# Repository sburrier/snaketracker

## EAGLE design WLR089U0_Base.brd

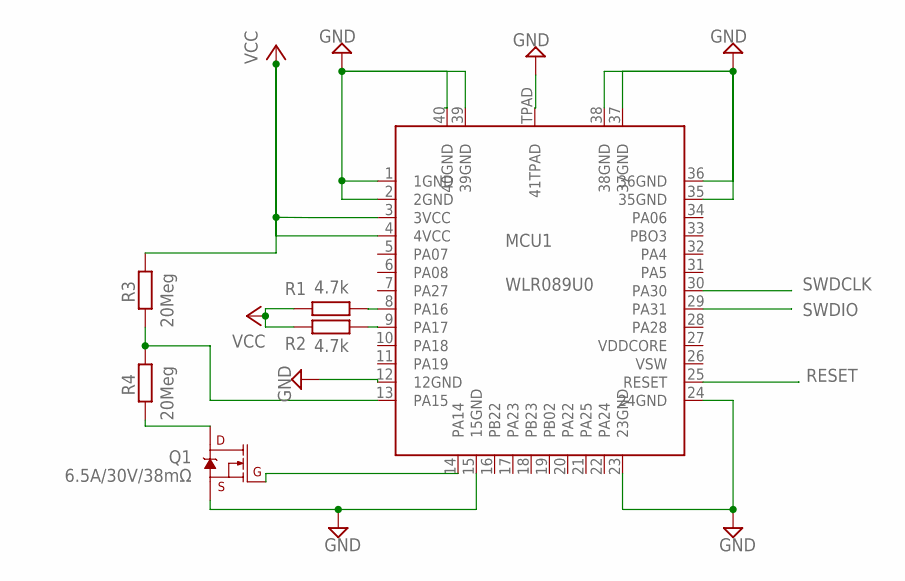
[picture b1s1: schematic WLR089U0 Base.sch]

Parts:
MCU1: WLR089U0
Q1: 6.5A/30V/38mΩ; SO08
R1, R2: 4.7k; SMK
R3, R4: 20Meg; SMK

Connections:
GND: MCU1.1 (1GND), MCU1.2 (2GND), MCU1.12 (12GND), MCU1.15 (15GND), MCU1.23 (23GND), MCU1.24 (24GND), MCU1.35 (35GND), MCU1.36 (36GND), MCU1.37 (37GND), MCU1.38 (38GND), MCU1.39 (39GND), MCU1.40 (40GND), MCU1.TPAD (41TPAD), Q1.1 (S), Q1.2 (S), Q1.3 (S)
unnamed: MCU1.8 (PA16), R1.1
unnamed: MCU1.9 (PA17), R2.1
unnamed: MCU1.14 (PA14), Q1.4 (G)
unnamed: Q1.5 (D), Q1.6 (D), Q1.7 (D), Q1.8 (D), R4.1
unnamed: MCU1.13 (PA15), R3.1, R4.2
RESET: MCU1.25 (RESET)
SWDCLK: MCU1.30 (PA30)
SWDIO: MCU1.29 (PA31)
VCC: MCU1.3 (3VCC), MCU1.4 (4VCC), R1.2, R2.2, R3.2

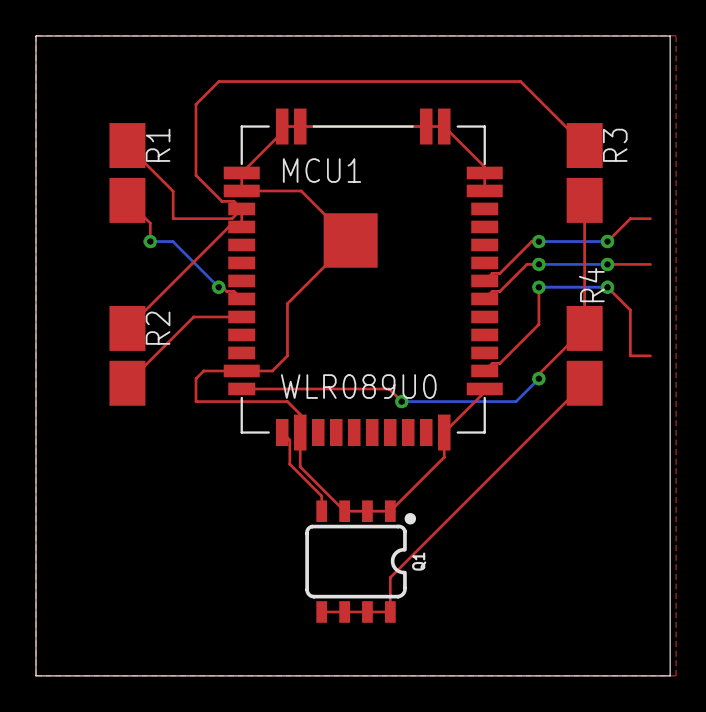
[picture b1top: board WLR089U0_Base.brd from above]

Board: 2 copper layers, 35.2 x 35.5 mm, 6 parts (0 on the bottom side), 7 nets.

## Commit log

2021-05-06 Add files via upload
    Configured MCU software, has an enabled sleep cycle, periodic transmission, and is configured to the 915MHz band

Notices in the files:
parts and their libraries:
SparkFun-DiscreteSemi: Licensing: Creative Commons ShareAlike 4.0 International - https://creativecommons.org/licenses/by-sa/4.0
